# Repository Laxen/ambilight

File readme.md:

### ESP32
* The ESP32-C3-MINI boards expose USB and have really good documentation
* ESP32 is generally cheaper and better than ESP8266 (faster CPU, BLE, more RAM/flash), and ESP8266 is not recommended for new designs
* The ESP32-WROOM boards don't expose the USB interface of the ESP32, which would then require an additional USB-to-UART component adding cost
* TODO: In the datasheet it says "USB Serial/JTAG Controller can also force the chip into Joint Download Boot mode from SPI Boot mode, as well as force the chip into SPI Boot mode from Joint Download Boot mode. For detailed information, please refer to Chapter 30 USB Serial/JTAG Controller (USB_SERIAL_JTAG).", can this be used to avoid buttons entirely? It would cut costs and make the device easier to use.

### USB-C Connector
* TYPE-C-31-M-12, provides USB 2.0 data lines in an easy-to-manufacture package

### ESD Protection
* USBLC6-2, common component specifically designed for USB 2.0
* Layout optimized to be close to USB-C connector, and have short traces for data and VBUS/GND
* 100nF between VBUS and GND was missed, but there's one not far away for the LDO which should be sufficient

### Level Shifter
* MCP1416, common component in a small package, enough current output for longer LED strip data lines
* ~SN74LVC1T45DBVR, only has 24mA output current, might not be enough for longer LED strip data lines~

### LDO
* AZ1117-3.3, common component, low enough dropout for 5V -> 3.3V, high enough current for ESP32, modern design that is compatible with low ESR ceramic caps
* ~AMS1117-3.3, common component, low enough dropout for 5V -> 3.3V, high enough current for ESP32, however it requires a tantalum cap on the output which is annoying~

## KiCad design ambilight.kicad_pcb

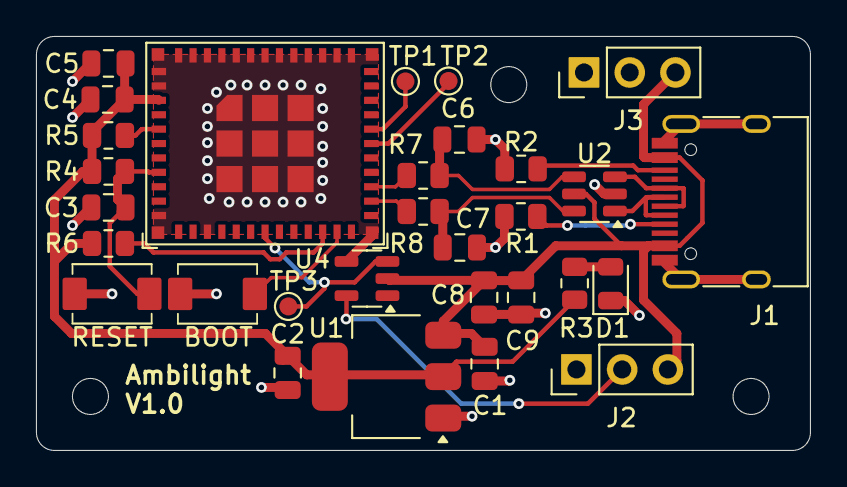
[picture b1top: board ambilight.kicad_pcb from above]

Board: 2 copper layers, 43.0 x 23.0 mm, 30 parts (0 on the bottom side), 20 nets.

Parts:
C1, C5: 10uF; C_0805_2012Metric
C2: 22uF; C_0805_2012Metric
C3, C9: 1uF; C_0805_2012Metric
C4, C8: 0.1uF; C_0805_2012Metric
C6, C7: TBD; C_0805_2012Metric
D1: LED; LED_0805_2012Metric
J1: TYPE-C-31-M-12; USB_C_Receptacle_HRO_TYPE-C-31-M-12
J2: RGB Connector; PinHeader_1x03_P2.54mm_Vertical
J3: Power Connector; PinHeader_1x03_P2.54mm_Vertical
R1, R2: 5.1k; R_0805_2012Metric
R3: 330R; R_0805_2012Metric
R4, R5, R6: 10k; R_0805_2012Metric
R7, R8: 0R; R_0805_2012Metric
SW1: RESET; TS-1088-AR02016
SW2: BOOT; TS-1088-AR02016
TP1, TP2, TP3: TestPoint_Pad_D1.0mm_SilkscreenFix
U1: AZ1117CH-3.3TRG1; SOT-223-3_TabPin2
U2: USBLC6-2SC6; SOT-23-6
U3: ESP32-C3-MINI-1-H4; ESP32-C3-MINI-1
U4: MCP1416; SOT-23-5

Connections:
+3V3: C2.1, C4.1, C5.1, R3.1, R4.1, R5.2, R6.2, U1.2 (VO), U3.3 (3V3)
/D+: R7.1, U3.27 (GPIO19/USB_D+)
/D-: R8.1, U3.26 (GPIO18/USB_D-)
/USBD+: C6.1, R7.2, U2.4 (I/O2)
/USBD-: C7.1, R8.2, U2.6 (I/O1)
GND: C1.2, C2.2, C3.2, C4.2, C5.2, C6.2, C7.2, C8.2, C9.2, D1.1 (K), J1.A1 (GND), J1.A12 (GND), J1.B1 (GND), J1.B12 (GND), J1.S1 (SHIELD), J2.1, J3.1, R1.2, R2.2, SW1.2, SW2.2, U1.1 (GND), U2.2 (GND), U3.1 (GND), U3.2 (GND), U3.11 (GND), U3.14 (GND), U3.36 (GND), U3.37 (GND), U3.38 (GND), U3.39 (GND), U3.40 (GND), U3.41 (GND), U3.42 (GND), U3.43 (GND), U3.44 (GND), U3.45 (GND), U3.46 (GND), U3.47 (GND), U3.48 (GND), U3.49 (GND), U3.50 (GND), U3.51 (GND), U3.52 (GND), U3.53 (GND), U4.4 (GND)
unnamed: D1.2 (A), R3.2
unnamed: J1.A5 (CC1), R1.1
unnamed: J1.B5 (CC2), R2.1
unnamed: J1.A6 (D+), J1.B6 (D+), U2.3 (I/O2)
unnamed: J1.A7 (D-), J1.B7 (D-), U2.1 (I/O1)
unnamed: J2.2, U4.5 (OUT)
unnamed: C3.1, R4.2, SW1.1, U3.8 (EN/CHIP_PU)
unnamed: R5.1, U3.5 (GPIO2/ADC1_CH2)
unnamed: TP3.1, U3.18 (GPIO4/ADC1_CH4), U4.3 (IN)
unnamed: R6.1, U3.22 (GPIO8)
unnamed: SW2.1, U3.23 (GPIO9)
unnamed: TP2.1, U3.30 (GPIO20/U0RXD)
unnamed: TP1.1, U3.31 (GPIO21/U0TXD)
VCC: C1.1, C8.1, C9.1, J1.A4 (VBUS), J1.A9 (VBUS), J1.B4 (VBUS), J1.B9 (VBUS), J2.3, J3.3, U1.3 (VI), U2.5 (VBUS), U4.2 (Vdd)

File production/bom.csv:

Designator,Footprint,Quantity,Value,LCSC Part #
"C1, C5",0805,2,10uF,
C2,0805,1,22uF,
"C3, C9",0805,2,1uF,
"C4, C8",0805,2,0.1uF,
D1,0805,1,LED,
J1,USB_C_Receptacle_HRO_TYPE-C-31-M-12,1,TYPE-C-31-M-12,
J2,PinHeader_1x03_P2.54mm_Vertical,1,RGB Connector,C49257
J3,PinHeader_1x03_P2.54mm_Vertical,1,Power Connector,C49257
"R1, R2",0805,2,5.1k,
R3,0805,1,330R,
"R4, R5, R6",0805,3,10k,
"R7, R8",0805,2,0R,
SW1,TS-1088-AR02016,1,RESET,C720477
SW2,TS-1088-AR02016,1,BOOT,C720477
U1,SOT-223-3_TabPin2,1,AZ1117CH-3.3TRG1,
U2,SOT-23-6,1,USBLC6-2SC6,
U3,ESP32-C3-MINI-1,1,ESP32-C3-MINI-1-H4,C41349510
U4,SOT-23-5,1,MCP1416,

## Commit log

2025-05-22 Initial commit
    Bit of a mess, some detail work for USB4085 -> FT230XS but not completed
    yet.
2025-05-24 Work on USB-C, FT230XS and LDO
2025-05-24 Use ESP32 instead, add readme
    The ESP32 makes a lot more sense in this application. The readme is very
    basic and will be used for explaining component choices, among other
    things in the future.
2025-05-27 Bunch of updates and beginning of PCB layout
2025-05-28 First draft of layout
2025-05-28 Some reordering
2025-05-28 Add ESD protection, reroute layout more efficiently
2025-06-02 Fix resistor values
2025-06-02 Minor layout adjustments
2025-06-02 Many small-ish changes, generate production files
    Some components were changed to get better deal at manufacturer. The
    files in the production folder are the ones sent to the manufacturer for
    this release.
